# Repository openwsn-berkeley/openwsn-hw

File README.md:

openwsn-hw
==========

OpenWSN hardware: boards and other designs

Part of UC Berkeley's OpenWSN project, http://www.openwsn.org/.

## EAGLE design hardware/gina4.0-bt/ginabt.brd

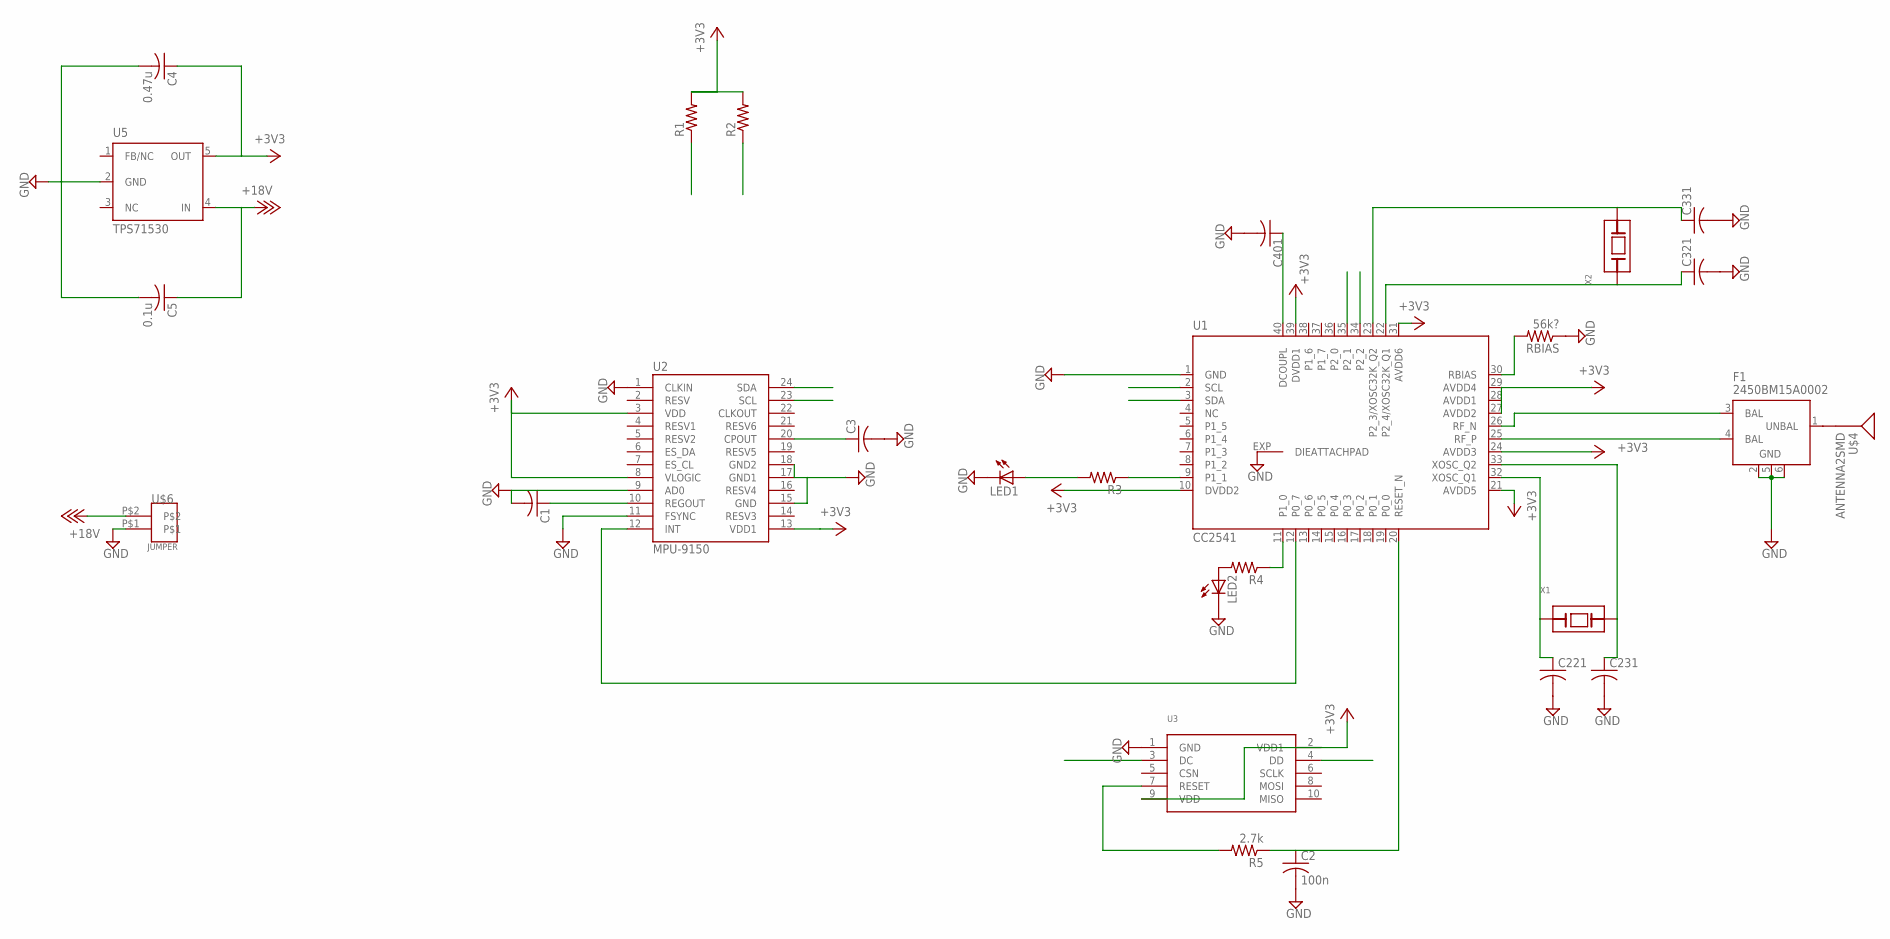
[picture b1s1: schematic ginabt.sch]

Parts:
C1, C3, C221, C231, C321, C331, C401: C-USC0402K; C0402K
C2: 100n; C0402K
C4: 0.47u; C0402K
C5: 0.1u; C0402K
F1: 2450BM15A0002
LED1, LED2: LED; SMARTLED-TTW
R1, R2, R3, R4: R-US_R0402; R0402
R5: 2.7k; R0402
RBIAS: 56k?; R0402
U1: CC2541; RHA_S-PVQFN-N40
U2: MPU-9150; LGA-24
U3: CCDEBUGGER; SMD-050-HEADER-2X5
U5: TPS71530; DCK_R-PDSO-G5
U$4: ANTENNA2SMD; ANTENNA-CHIP2
U$6: JUMPER; JUMPER_1X2_80MIL
X1: XTALABS07; ABS07
X2: XTALCX3225SA; CX3225SA

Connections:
+3V3: C4.1, R1.2, R2.2, U1.10 (DVDD2), U1.21 (AVDD5), U1.24 (AVDD3), U1.27 (AVDD2), U1.28 (AVDD1), U1.29 (AVDD4), U1.31 (AVDD6), U1.39 (DVDD1), U2.3 (VDD), U2.8 (VLOGIC), U2.13 (VDD1), U3.2 (VDD1), U3.9 (VDD), U5.5 (OUT)
+18V: C5.1, U5.4 (IN), U$6.P$2
DC: U1.34 (P2_2), U3.3 (DC)
DD: U1.35 (P2_1), U3.4 (DD)
GND: C1.2, C2.2, C3.2, C4.2, C5.2, C221.2, C231.2, C321.2, C331.2, C401.2, F1.2 (GND), F1.5 (GND), F1.6 (GND), LED1.C@1 (C), LED2.C@1 (C), RBIAS.1, U1.1 (GND), U1.EXP (DIEATTACHPAD), U2.1 (CLKIN), U2.9 (AD0), U2.11 (FSYNC), U2.15 (GND), U2.17 (GND1), U2.18 (GND2), U3.1 (GND), U5.2 (GND), U$6.P$1
unnamed: C401.1, U1.40 (DCOUPL)
unnamed: LED2.A@1 (A), R4.2
unnamed: R4.1, U1.11 (P1_0)
unnamed: C221.1, U1.32 (XOSC_Q1), X1.1 (A)
unnamed: C231.1, U1.33 (XOSC_Q2), X1.2 (B)
unnamed: C321.1, U1.22 (P2_4/XOSC32K_Q1), X2.3 (A)
unnamed: C331.1, U1.23 (P2_3/XOSC32K_Q2), X2.1 (B)
unnamed: F1.3 (BAL), U1.26 (RF_N)
unnamed: F1.4 (BAL), U1.25 (RF_P)
unnamed: C1.1, U2.10 (REGOUT)
unnamed: F1.1 (UNBAL), U$4.FEED
unnamed: U1.12 (P0_7), U2.12 (INT)
unnamed: R3.1, U1.9 (P1_1)
unnamed: C3.1, U2.20 (CPOUT)
unnamed: LED1.A@1 (A), R3.2
unnamed: RBIAS.2, U1.30 (RBIAS)
unnamed: R5.2, U3.7 (RESET)
unnamed: C2.1, R5.1, U1.20 (RESET_N)
NC: U5.3 (NC)
SCL: R1.1, U1.2 (SCL), U2.23 (SCL)
SDA: R2.1, U1.3 (SDA), U2.24 (SDA)

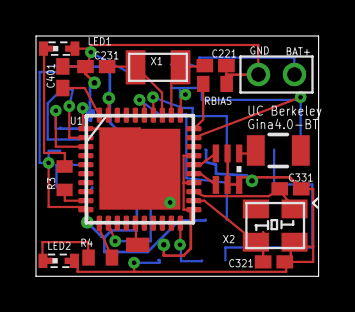
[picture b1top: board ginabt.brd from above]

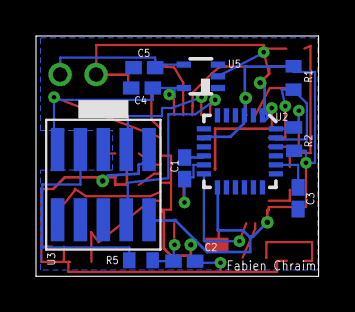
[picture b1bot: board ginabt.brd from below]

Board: 2 copper layers, 15.7 x 13.3 mm, 27 parts (11 on the bottom side), 25 nets.

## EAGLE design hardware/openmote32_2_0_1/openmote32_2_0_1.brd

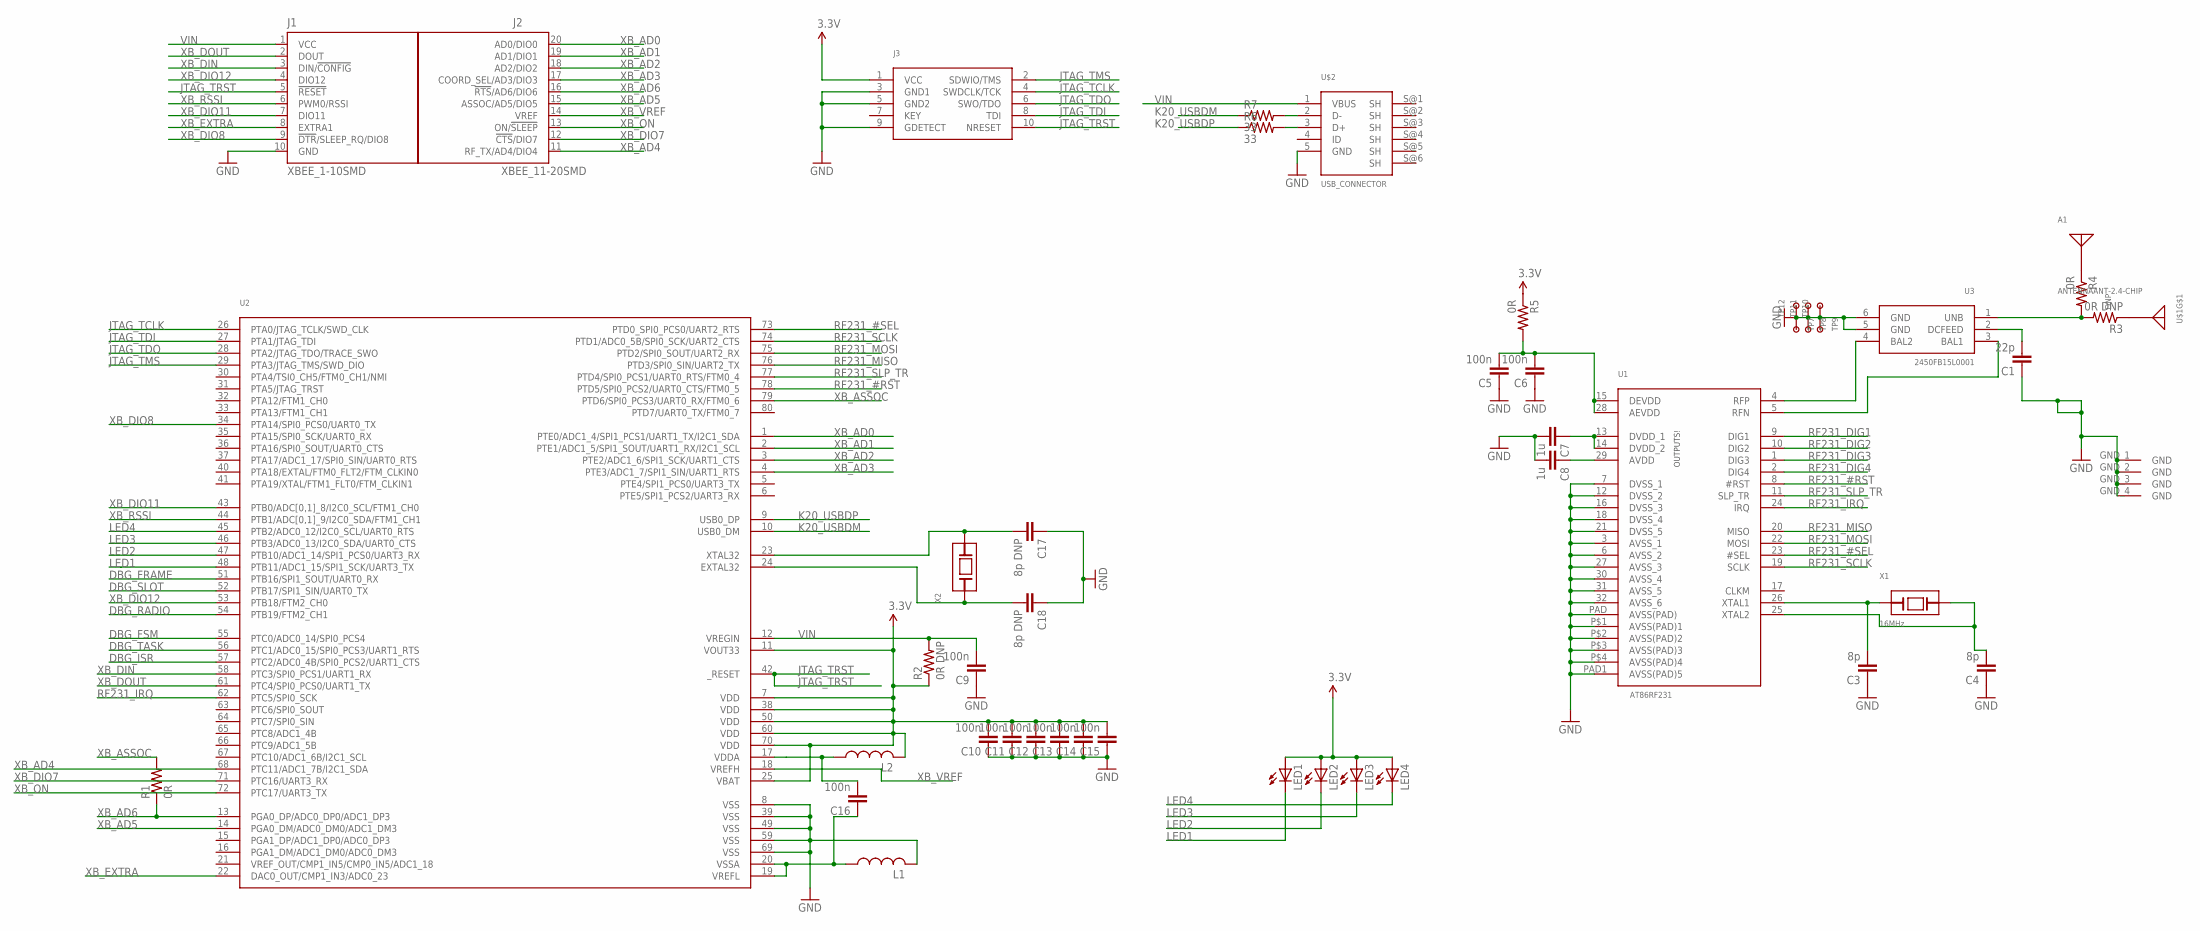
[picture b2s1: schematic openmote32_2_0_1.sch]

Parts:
A1: ANTENNAANT-2.4-CHIP; ANT-2.4-CHP
C1: 22p; C0402
C3, C4: 8p; C0402
C5, C6, C9, C10, C11, C12, C13, C14, C15, C16: 100n; C0402
C7, C8: 1u; C0402
C17, C18: 8p DNP; C0402
J1: XBEE_1-10SMD; XBEE_1-10+SMD
J2: XBEE_11-20SMD; XBEE_11-20+SMD
J3: JTAG_CONNECTOR; SMD-050-HEADER-2X5
L1, L2: L-USL0402; L0402
LED1, LED2, LED3, LED4: LEDCHIPLED_0603; CHIPLED_0603
R1, R4, R5: 0R; R0402
R2, R3: 0R DNP; R0402
R6, R7: 33; R0402
TP7, TP8, TP9, TP10, TP11, TP12: TESTPOINTSMALLEST; TESTPOINT
U1: AT86RF231; ATRF231_32QN2
U2: K20_80PIN; K20_LQFP80
U3: 2450FB15L0001
U$1: DNP; CONREVSMA003.031
U$2: USB_CONNECTOR; MICROUSB_10118192
X1: 16MHz; CX3225SA
X2: XTALABS07; ABS07

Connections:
3.3V: C10.2, C11.2, C12.2, C13.2, C14.2, C15.2, J3.1 (VCC), L2.2, LED1.A, LED2.A, LED3.A, LED4.A, R2.1, R5.1, U2.7 (VDD), U2.11 (VOUT33), U2.25 (VBAT), U2.38 (VDD), U2.50 (VDD), U2.60 (VDD), U2.70 (VDD)
DBG_FRAME: U2.51 (PTB16/SPI1_SOUT/UART0_RX)
DBG_FSM: U2.55 (PTC0/ADC0_14/SPI0_PCS4)
DBG_ISR: U2.57 (PTC2/ADC0_4B/SPI0_PCS2/UART1_CTS)
DBG_RADIO: U2.54 (PTB19/FTM2_CH1)
DBG_SLOT: U2.52 (PTB17/SPI1_SIN/UART0_TX)
DBG_TASK: U2.56 (PTC1/ADC0_15/SPI0_PCS3/UART1_RTS)
GND: C1.1, C3.1, C4.1, C5.1, C6.1, C7.2, C8.2, C9.1, C10.1, C11.1, C12.1, C13.1, C14.1, C15.1, C17.1, C18.1, J1.10 (GND), J3.3 (GND1), J3.5 (GND2), J3.9 (GDETECT), L1.2, TP7.P$1, TP8.P$1, TP9.P$1, TP10.P$1, TP11.P$1, TP12.P$1, U1.3 (AVSS_1), U1.6 (AVSS_2), U1.7 (DVSS_1), U1.12 (DVSS_2), U1.16 (DVSS_3), U1.18 (DVSS_4), U1.21 (DVSS_5), U1.27 (AVSS_3), U1.30 (AVSS_4), U1.31 (AVSS_5), U1.32 (AVSS_6), U1.P$1 (AVSS(PAD)1), U1.P$2 (AVSS(PAD)2), U1.P$3 (AVSS(PAD)3), U1.P$4 (AVSS(PAD)4), U1.PAD (AVSS(PAD)), U1.PAD1 (AVSS(PAD)5), U2.8 (VSS), U2.39 (VSS), U2.49 (VSS), U2.59 (VSS), U2.69 (VSS), U3.5 (GND), U3.6 (GND), U$1.GND_1 (GND), U$1.GND_2 (GND), U$1.GND_3 (GND), U$1.GND_4 (GND), U$2.5 (GND)
JTAG_TCLK: J3.4 (SWDCLK/TCK), U2.26 (PTA0/JTAG_TCLK/SWD_CLK)
JTAG_TDI: J3.8 (TDI), U2.27 (PTA1/JTAG_TDI)
JTAG_TDO: J3.6 (SWO/TDO), U2.28 (PTA2/JTAG_TDO/TRACE_SWO)
JTAG_TMS: J3.2 (SDWIO/TMS), U2.29 (PTA3/JTAG_TMS/SWD_DIO)
JTAG_TRST: J1.5 (!RESET), J3.10 (NRESET), U2.42 (_RESET)
K20_USBDM: R7.1, U2.10 (USB0_DM)
K20_USBDP: R6.1, U2.9 (USB0_DP)
LED1: LED1.C, U2.48 (PTB11/ADC1_15/SPI1_SCK/UART3_TX)
LED2: LED2.C, U2.47 (PTB10/ADC1_14/SPI1_PCS0/UART3_RX)
LED3: LED3.C, U2.46 (PTB3/ADC0_13/I2C0_SDA/UART0_CTS)
LED4: LED4.C, U2.45 (PTB2/ADC0_12/I2C0_SCL/UART0_RTS)
unnamed: U1.4 (RFP), U3.4 (BAL2)
unnamed: U1.5 (RFN), U3.3 (BAL1)
unnamed: R3.2, R4.2, U3.1 (UNB)
unnamed: C1.2, U3.2 (DCFEED)
unnamed: R6.2, U$2.3 (D+)
unnamed: C3.2, U1.26 (XTAL1), X1.3 (A)
unnamed: C4.2, U1.25 (XTAL2), X1.1 (B)
unnamed: C18.2, U2.24 (EXTAL32), X2.1 (A)
unnamed: C8.1, U1.29 (AVDD)
unnamed: C7.1, U1.13 (DVDD_1), U1.14 (DVDD_2)
unnamed: C17.2, U2.23 (XTAL32), X2.2 (B)
unnamed: A1.CON, R4.1
unnamed: C16.1, L1.1, U2.19 (VREFL), U2.20 (VSSA)
unnamed: R3.1, U$1.CON
unnamed: C16.2, L2.1, U2.17 (VDDA)
unnamed: C5.2, C6.2, R5.2, U1.15 (DEVDD), U1.28 (AEVDD)
unnamed: R7.2, U$2.2 (D-)
RF231_#RST: U1.8 (#RST), U2.78 (PTD5/SPI0_PCS2/UART0_CTS/FTM0_5)
RF231_#SEL: U1.23 (#SEL), U2.73 (PTD0_SPI0_PCS0/UART2_RTS)
RF231_DIG1: U1.9 (DIG1)
RF231_DIG2: U1.10 (DIG2)
RF231_DIG3: U1.1 (DIG3)
RF231_DIG4: U1.2 (DIG4)
RF231_IRQ: U1.24 (IRQ), U2.62 (PTC5/SPI0_SCK)
RF231_MISO: U1.20 (MISO), U2.76 (PTD3/SPI0_SIN/UART2_TX)
RF231_MOSI: U1.22 (MOSI), U2.75 (PTD2/SPI0_SOUT/UART2_RX)
RF231_SCLK: U1.19 (SCLK), U2.74 (PTD1/ADC0_5B/SPI0_SCK/UART2_CTS)
RF231_SLP_TR: U1.11 (SLP_TR), U2.77 (PTD4/SPI0_PCS1/UART0_RTS/FTM0_4)
VIN: C9.2, J1.1 (VCC), R2.2, U2.12 (VREGIN), U$2.1 (VBUS)
XB_AD0: J2.20 (AD0/DIO0), U2.1 (PTE0/ADC1_4/SPI1_PCS1/UART1_TX/I2C1_SDA)
XB_AD1: J2.19 (AD1/DIO1), U2.2 (PTE1/ADC1_5/SPI1_SOUT/UART1_RX/I2C1_SCL)
XB_AD2: J2.18 (AD2/DIO2), U2.3 (PTE2/ADC1_6/SPI1_SCK/UART1_CTS)
XB_AD3: J2.17 (COORD_SEL/AD3/DIO3), U2.4 (PTE3/ADC1_7/SPI1_SIN/UART1_RTS)
XB_AD4: J2.11 (RF_TX/AD4/DIO4), U2.68 (PTC11/ADC1_7B/I2C1_SDA)
XB_AD5: J2.15 (ASSOC/AD5/DIO5), U2.14 (PGA0_DM/ADC0_DM0/ADC1_DM3)
XB_AD6: J2.16 (!RTS!/AD6/DIO6), R1.1, U2.13 (PGA0_DP/ADC0_DP0/ADC1_DP3)
XB_ASSOC: R1.2, U2.79 (PTD6/SPI0_PCS3/UART0_RX/FTM0_6)
XB_DIN: J1.3 (DIN/!CONFIG), U2.58 (PTC3/SPI0_PCS1/UART1_RX)
XB_DIO7: J2.12 (!CTS!/DIO7), U2.71 (PTC16/UART3_RX)
XB_DIO8: J1.9 (!DTR!/SLEEP_RQ/DIO8), U2.34 (PTA14/SPI0_PCS0/UART0_TX)
XB_DIO11: J1.7 (DIO11), U2.43 (PTB0/ADC[0,1]_8/I2C0_SCL/FTM1_CH0)
XB_DIO12: J1.4 (DIO12), U2.53 (PTB18/FTM2_CH0)
XB_DOUT: J1.2 (DOUT), U2.61 (PTC4/SPI0_PCS0/UART1_TX)
XB_EXTRA: J1.8 (EXTRA1), U2.22 (DAC0_OUT/CMP1_IN3/ADC0_23)
XB_ON: J2.13 (ON/!SLEEP), U2.72 (PTC17/UART3_TX)
XB_RSSI: J1.6 (PWM0/RSSI), U2.44 (PTB1/ADC[0,1]_9/I2C0_SDA/FTM1_CH1)
XB_VREF: J2.14 (VREF), U2.18 (VREFH)

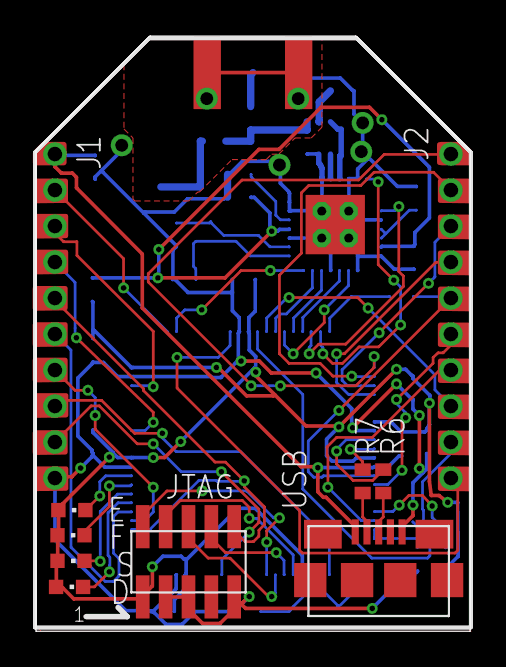
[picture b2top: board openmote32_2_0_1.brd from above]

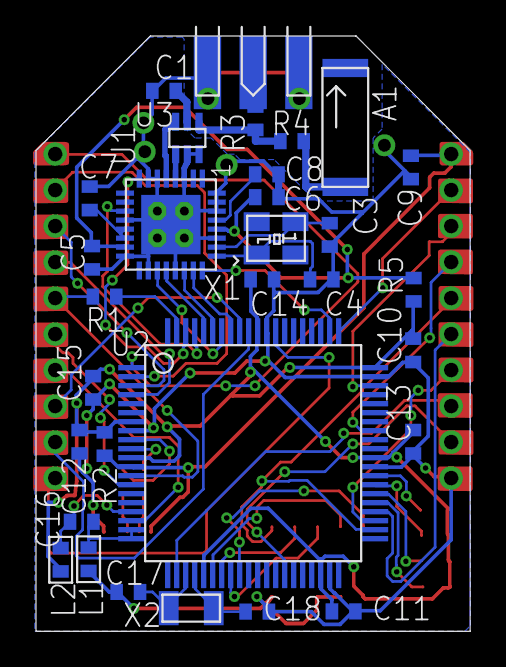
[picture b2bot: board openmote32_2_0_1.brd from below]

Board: 2 copper layers, 24.1 x 33.1 mm, 47 parts (31 on the bottom side), 56 nets.

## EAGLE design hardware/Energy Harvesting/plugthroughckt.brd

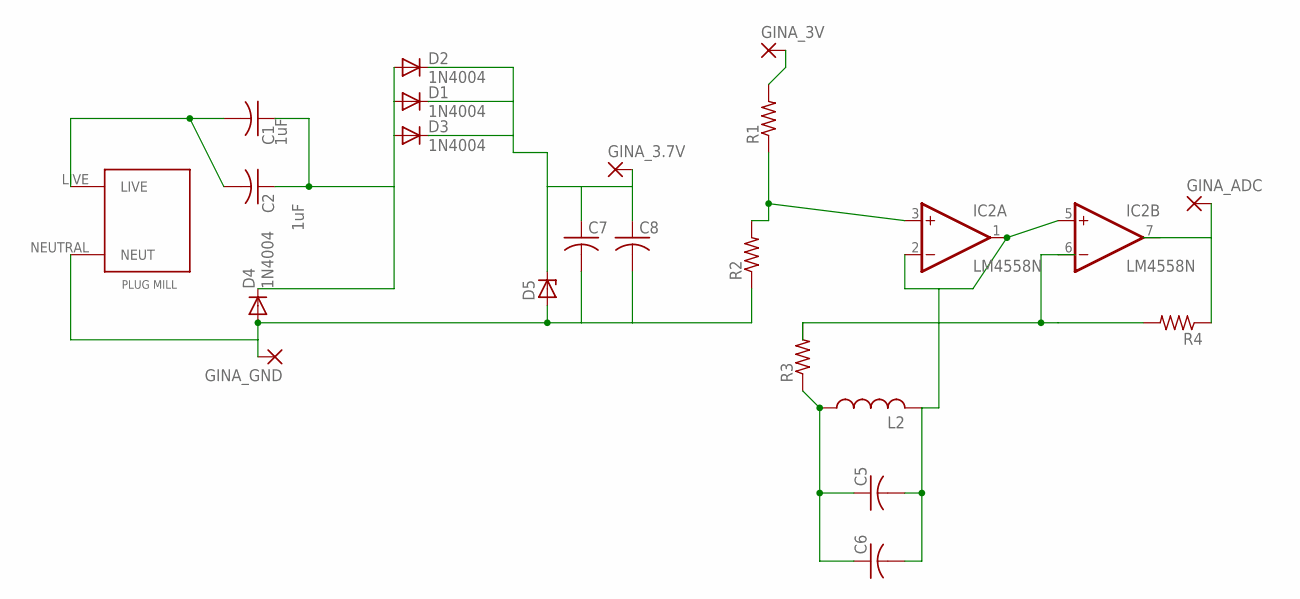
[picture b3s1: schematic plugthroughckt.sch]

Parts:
C1, C2, C5, C6: C-US075-032X103; C075-032X103
C7, C8: C-US025-050X050; C025-050X050
D1, D2, D3, D4: 1N4004; DO41-10
D5: ZENER-DIODEDO41Z10; DO41Z10
GINA_3.7V, GINA_3V: 3,81/1,4
GINA_ADC: 3,81/1,4
GINA_GND: 3,81/1,4
IC2: LM4558N; DIL08
L2: L-US0207/5V; 0207/5V
R1, R2, R3, R4: R-US_0207/10; 0207/10
U$1: PLUGMILL

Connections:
unnamed: C1.2, C2.2, U$1.LIVE
unnamed: IC2.3 (+IN), R1.1, R2.2
unnamed: GINA_ADC.1, IC2.7 (OUT), R4.1
unnamed: IC2.6 (-IN), R3.2, R4.2
unnamed: C5.1, C6.1, L2.1, R3.1
unnamed: GINA_3V.1, R1.2
unnamed: C1.1, C2.1, D1.A, D2.A, D3.A, D4.C
unnamed: C5.2, C6.2, IC2.1 (OUT), IC2.2 (-IN), IC2.5 (+IN), L2.2
V+: C7.1, C8.1, D1.C, D2.C, D3.C, D5.C, GINA_3.7V.1, IC2.8 (V+)
V-: C7.2, C8.2, D4.A, D5.A, GINA_GND.1, IC2.4 (V-), R2.1, U$1.NEUTRAL (NEUT)

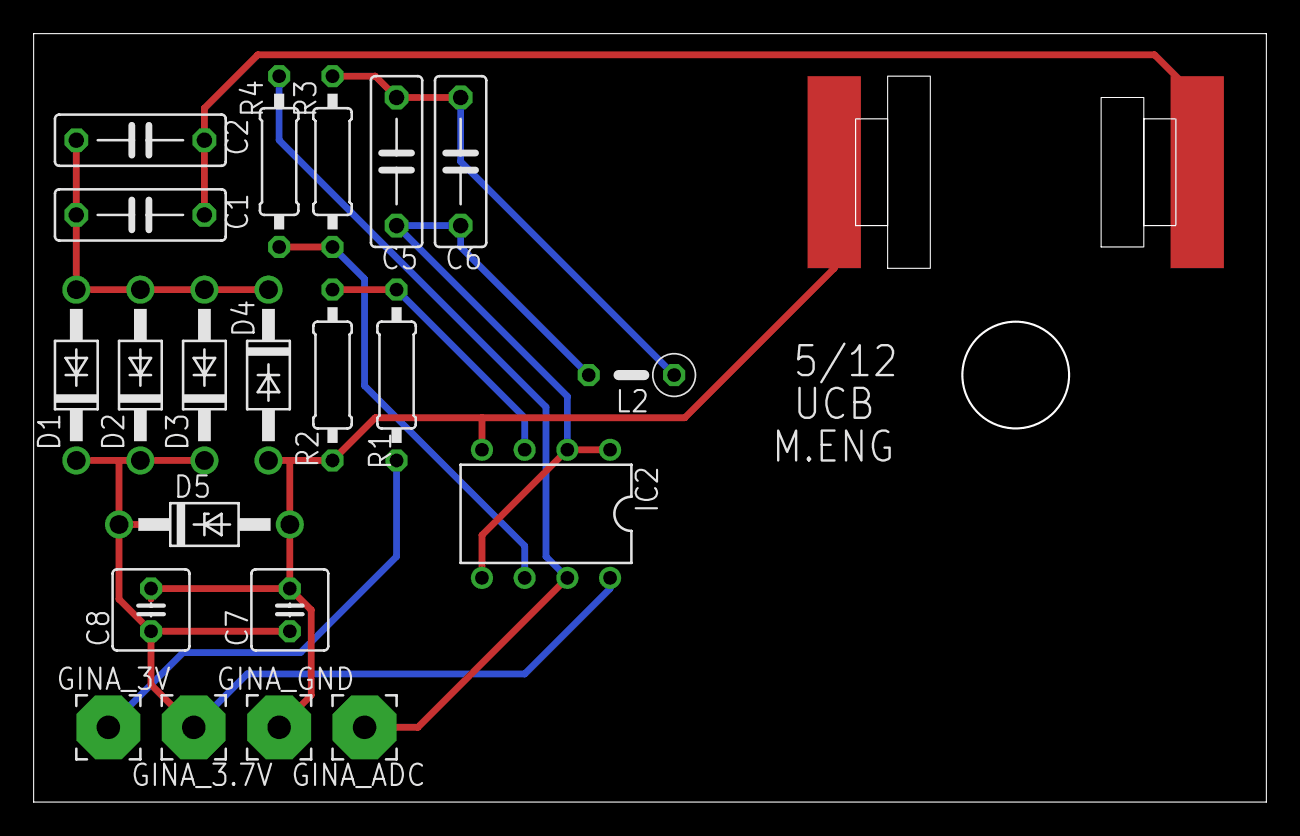
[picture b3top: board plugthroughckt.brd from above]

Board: 2 copper layers, 73.3 x 45.7 mm, 22 parts (0 on the bottom side), 10 nets.

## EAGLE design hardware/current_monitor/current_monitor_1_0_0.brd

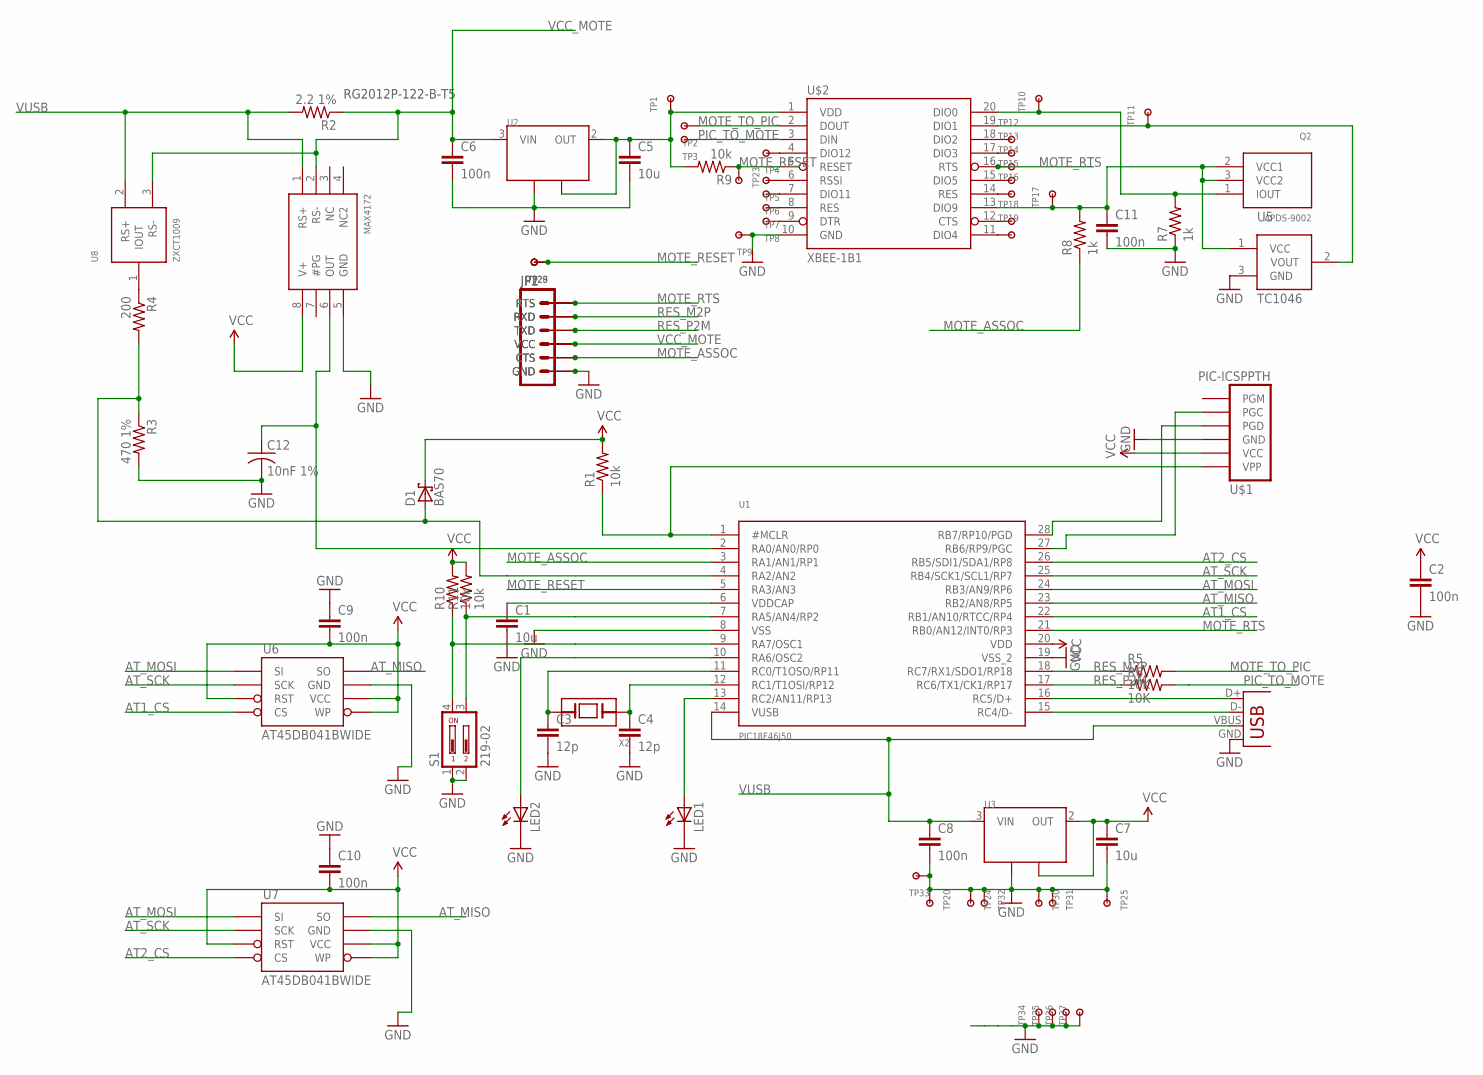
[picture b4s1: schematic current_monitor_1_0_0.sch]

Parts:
C1, C5, C7: 10u; 0805
C2, C6, C8, C9, C10, C11: 100n; 0805
C3, C4: 12p; 0805
C12: 10nF 1%; C1812
D1: BAS70; SOT23
JP1, JP2: FTDI_CABLESIP; 1X06
LED1, LED2: LEDCHIP-LED0805; CHIP-LED0805
Q2: APDS-9002
R1, R9, R10, R11: 10k; 0805
R2: 2.2 1%; 0805
R3: 470 1%; 0805
R4: 200; 0805
R5, R6: 10K; 0805
R7, R8: 1k; 0805
S1: 219-02; CTS-219-02
TP1, TP2, TP3, TP4, TP5, TP6, TP7, TP8, TP9, TP10, TP11, TP12, TP13, TP14, TP15, TP16, TP17, TP18, TP19, TP23, TP28, TP29: TESTPOINT100MIL; TESTPOINT-100MIL
TP20, TP24, TP25, TP30, TP31, TP32, TP33: TESTPOINTSMALLEST; TESTPOINT
TP34, TP35, TP36, TP37: TESTPOINTM3; M3_HOLE
U1: PIC18F46J50; SO28W
U2, U3: NX1117C; SOT223
U4: MAX4172; SO08
U5: TC1046; SOT23
U6, U7: AT45DB041BWIDE; SO08WIDE
U8: ZXCT1009; SOT23
U$1: PIC-ICSPPTH; MOLEX-1X6
U$2: XBEE-1B1; XBEE-1
X1: USBSMD; USB-MINIB
X2: XTALABS07; ABS07

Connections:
AT1_CS: U1.22 (RB1/AN10/RTCC/RP4), U6.4 (CS)
AT2_CS: U1.26 (RB5/SDI1/SDA1/RP8), U7.4 (CS)
AT_MISO: U1.23 (RB2/AN8/RP5), U6.8 (SO), U7.8 (SO)
AT_MOSI: U1.24 (RB3/AN9/RP6), U6.1 (SI), U7.1 (SI)
AT_SCK: U1.25 (RB4/SCK1/SCL1/RP7), U6.2 (SCK), U7.2 (SCK)
EXTRA1: R11.1, S1.3, U1.7 (RA5/AN4/RP2)
EXTRA2: R10.1, S1.4, U1.9 (RA7/OSC1)
EXTRA3: LED2.A, U1.10 (RA6/OSC2)
GND: C1.2, C2.2, C3.2, C4.2, C5.2, C6.2, C7.2, C8.2, C9.1, C10.1, C11.2, C12.2, JP1.1 (GND), JP2.1 (GND), LED1.C, LED2.C, R3.2, R7.1, S1.1, S1.2, TP9.2, TP20.P$1, TP24.P$1, TP25.P$1, TP30.P$1, TP31.P$1, TP32.P$1, TP33.P$1, TP34.P$1, TP35.P$1, TP36.P$1, TP37.P$1, U1.8 (VSS), U1.19 (VSS_2), U2.1 (GND), U3.1 (GND), U4.5 (GND), U5.3 (GND), U6.7 (GND), U7.7 (GND), U$1.4 (GND), U$2.10 (GND), X1.GND
MOTE_ASSOC: JP1.2 (CTS), JP2.2 (CTS), R8.1, U1.3 (RA1/AN1/RP1)
MOTE_RESET: R9.1, TP23.2, TP28.2, TP29.2, U1.5 (RA3/AN3), U$2.5 (RESET)
MOTE_RTS: JP1.6 (RTS), JP2.6 (RTS), TP14.2, U1.21 (RB0/AN12/INT0/RP3), U$2.16 (RTS)
MOTE_TO_PIC: R5.2, TP2.2, U$2.2 (DOUT)
unnamed: U1.16 (RC5/D+), X1.D+
unnamed: U1.15 (RC4/D-), X1.D-
unnamed: LED1.A, U1.13 (RC2/AN11/RP13)
unnamed: C1.1, U1.6 (VDDCAP)
unnamed: R1.1, U1.1 (#MCLR), U$1.6 (VPP)
unnamed: C4.1, U1.12 (RC1/T1OSI/RP12), X2.1 (A)
unnamed: C3.1, U1.11 (RC0/T1OSO/RP11), X2.2 (B)
unnamed: U1.28 (RB7/RP10/PGD), U$1.3 (PGD)
unnamed: U1.27 (RB6/RP9/PGC), U$1.2 (PGC)
unnamed: C5.1, R9.2, TP1.2, U2.2 (OUT), U2.4 (TAB), U$2.1 (VDD)
unnamed: C12.1, U1.2 (RA0/AN0/RP0), U4.6 (OUT)
unnamed: D1.1 (A), R3.1, R4.2, U1.4 (RA2/AN2)
unnamed: R4.1, U8.1 (IOUT)
unnamed: C11.1, Q2.2 (VCC1), Q2.3 (VCC2), R8.2, TP17.2, U5.1 (VCC), U$2.13 (DIO9)
unnamed: Q2.1 (IOUT), R7.2, TP10.2, U$2.20 (DIO0)
unnamed: TP11.2, U5.2 (VOUT), U$2.19 (DIO1)
unnamed: TP4.2, U$2.4 (DIO12)
unnamed: TP5.2, U$2.6 (RSSI)
unnamed: TP6.2, U$2.7 (DIO11)
unnamed: TP7.2, U$2.8 (RES)
unnamed: TP8.2, U$2.9 (DTR)
unnamed: TP12.2, U$2.18 (DIO2)
unnamed: TP13.2, U$2.17 (DIO3)
unnamed: TP15.2, U$2.15 (DIO5)
unnamed: TP16.2, U$2.14 (RES)
unnamed: TP18.2, U$2.12 (CTS)
unnamed: TP19.2, U$2.11 (DIO4)
PIC_TO_MOTE: R6.2, TP3.2, U$2.3 (DIN)
RES_M2P: JP1.5 (RXD), JP2.5 (RXD), R5.1, U1.18 (RC7/RX1/SDO1/RP18)
RES_P2M: JP1.4 (TXD), JP2.4 (TXD), R6.1, U1.17 (RC6/TX1/CK1/RP17)
VCC: C2.1, C7.1, C9.2, C10.2, D1.3 (C), R1.2, R10.2, R11.2, U1.20 (VDD), U3.2 (OUT), U3.4 (TAB), U4.8 (V+), U6.3 (RST), U6.5 (WP), U6.6 (VCC), U7.3 (RST), U7.5 (WP), U7.6 (VCC), U$1.5 (VCC)
VCC_MOTE: C6.1, JP1.3 (VCC), JP2.3 (VCC), R2.1, U2.3 (VIN), U4.2 (RS-), U8.3 (RS-)
VUSB: C8.1, R2.2, U1.14 (VUSB), U3.3 (VIN), U4.1 (RS+), U8.2 (RS+), X1.VBUS

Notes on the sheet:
RG2012P-122-B-T5

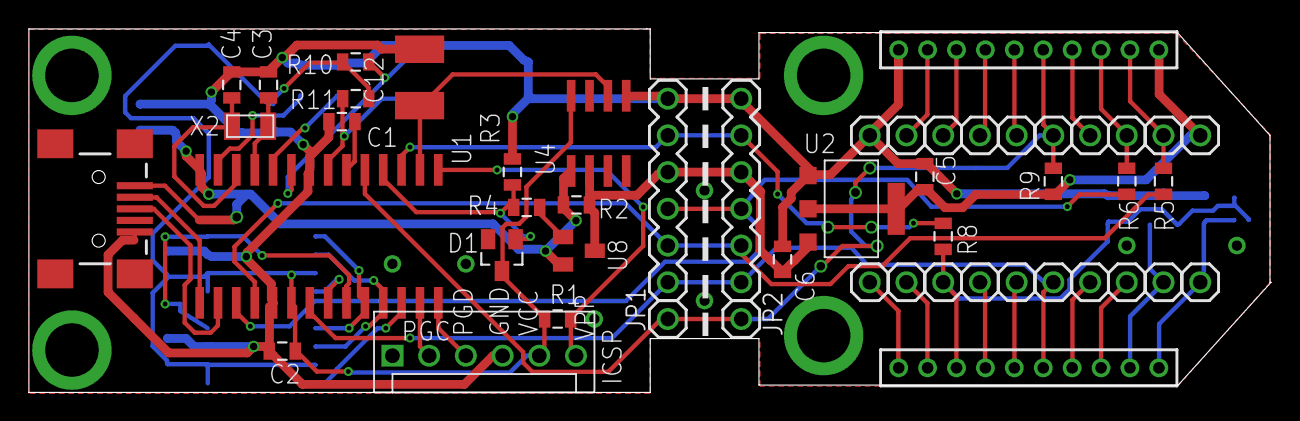
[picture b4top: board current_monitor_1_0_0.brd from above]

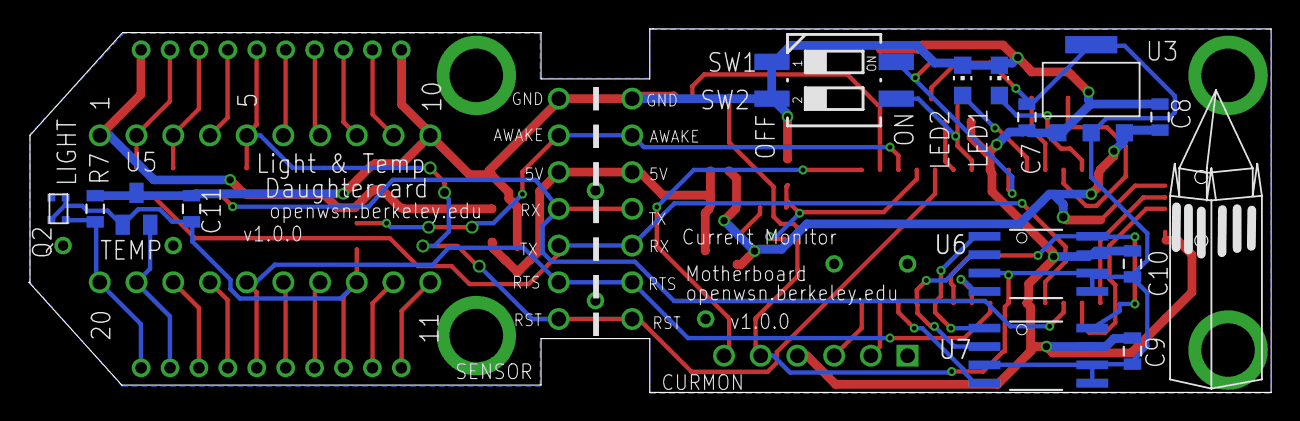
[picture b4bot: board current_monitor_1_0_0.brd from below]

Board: 2 copper layers, 85.9 x 25.1 mm, 76 parts (15 on the bottom side), 46 nets.

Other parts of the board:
U$4: SATHER_TOWER

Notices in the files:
parts and their libraries:
sparkfun: Licensing: CC v3.0 Share-Alike You are welcome to use this library for commercial purposes.
